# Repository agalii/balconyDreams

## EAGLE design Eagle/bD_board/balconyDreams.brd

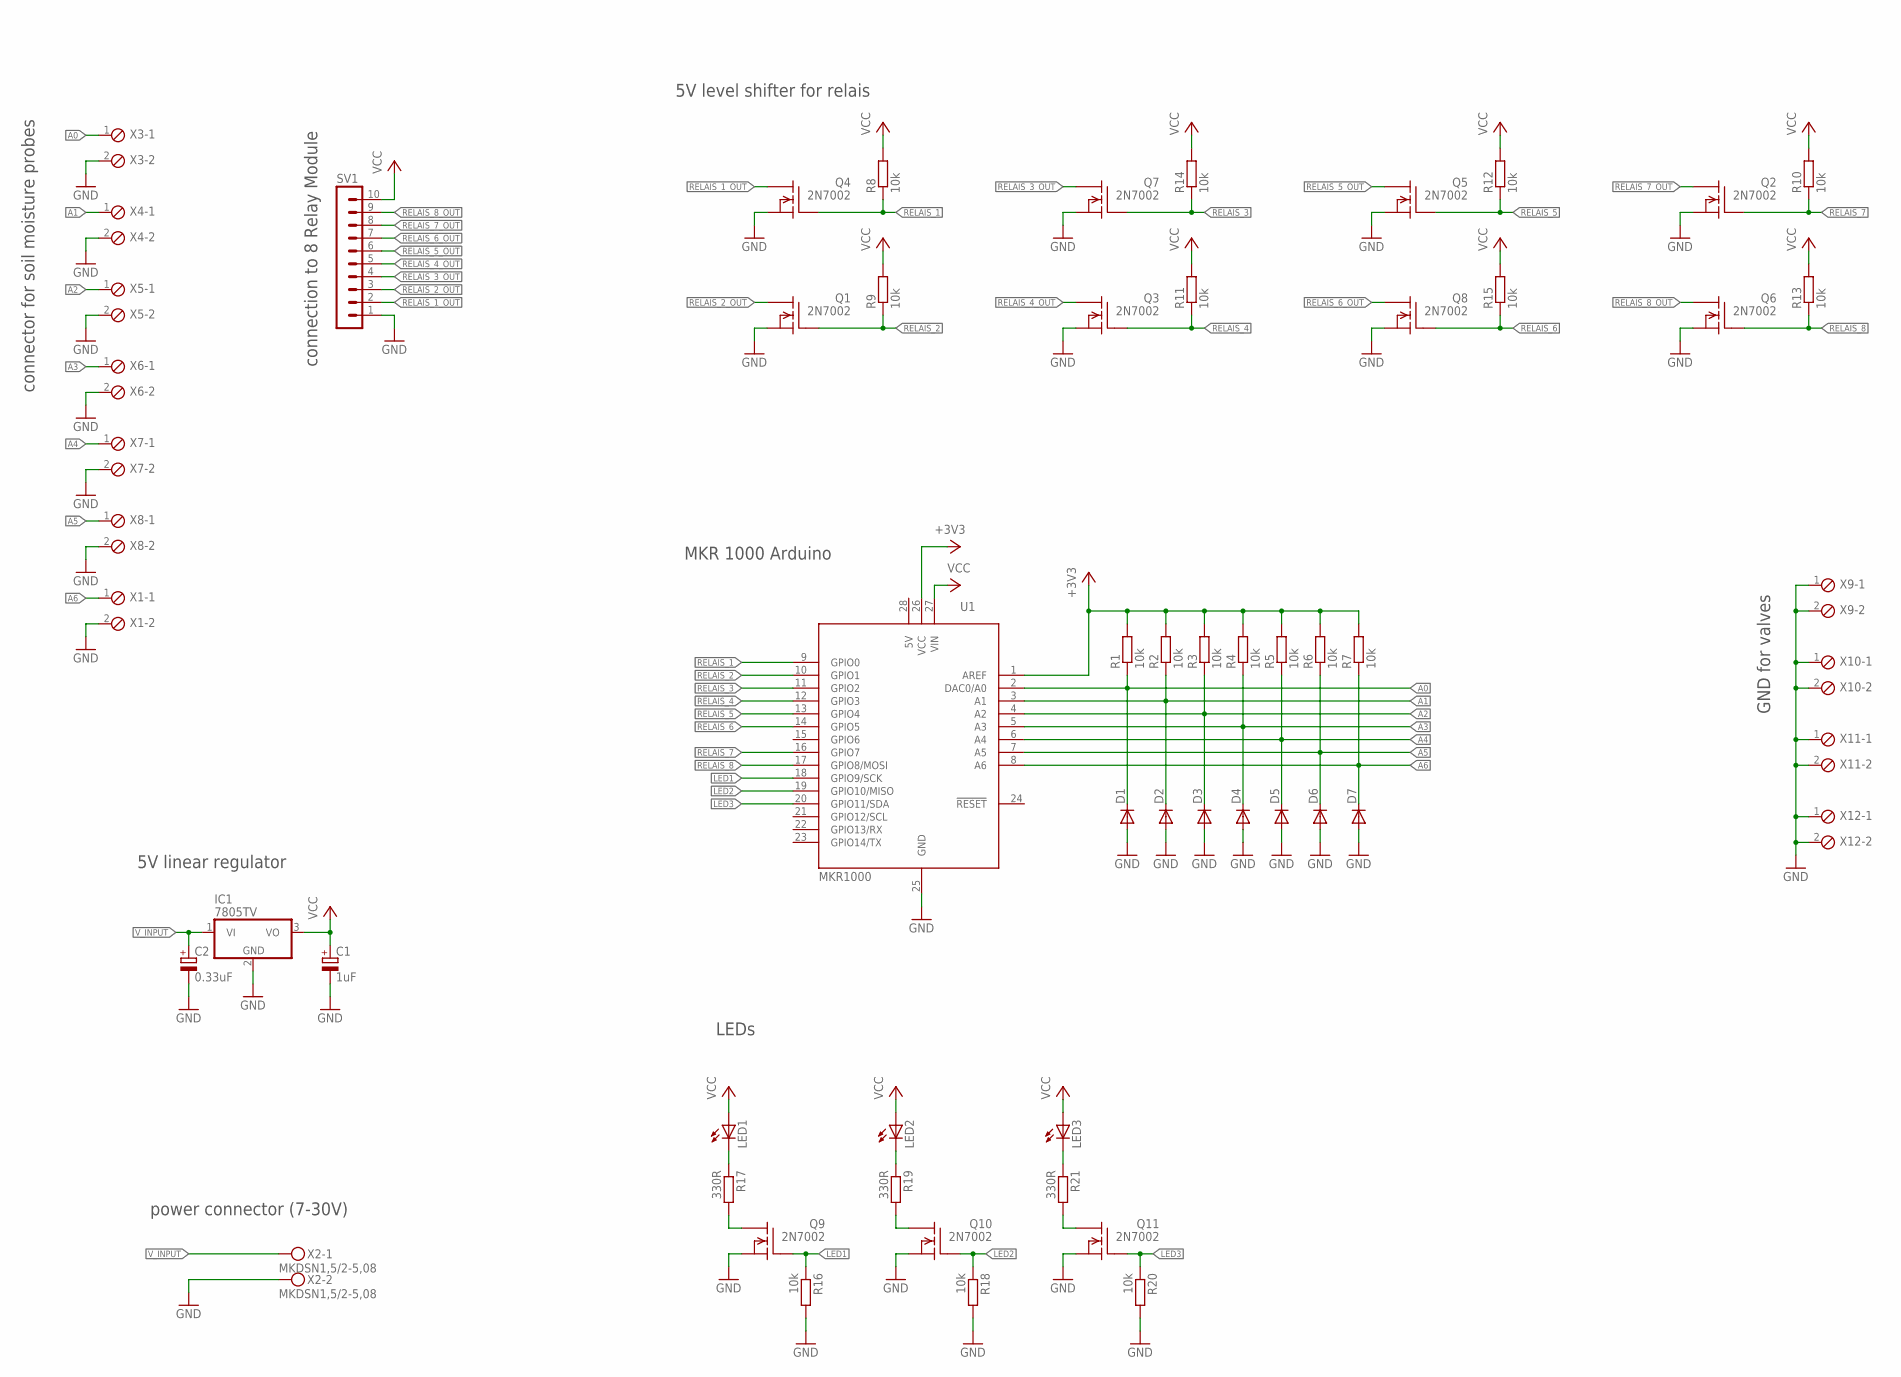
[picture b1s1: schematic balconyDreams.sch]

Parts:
C1: 1uF; E5-6
C2: 0.33uF; E5-6
D1, D2, D3, D4, D5, D6, D7: DIODE-SOD323-W; SOD323-W
IC1: 7805TV; TO220V
LED1, LED2, LED3: LEDCHIPLED_0805; CHIPLED_0805
Q1, Q2, Q3, Q4, Q5, Q6, Q7, Q8, Q9, Q10, Q11: 2N7002; SOT23
R1, R2, R3, R4, R5, R6, R7, R8, R9, R10, R11, R12, R13, R14, R15, R16, R18, R20: 10k; R0805
R17, R19, R21: 330R; R0805
SV1: MA10-1
U1: MKR1000
X1, X3, X4, X5, X6, X7, X8, X9, X10, X11, X12: MPT2; 2POL254
X2: MKDSN1,5/2-5,08

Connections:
+3V3: R1.2, R2.2, R3.2, R4.2, R5.2, R6.2, R7.2, U1.1 (AREF), U1.26 (VCC)
A0: D1.C, R1.1, U1.2 (DAC0/A0), X3.1
A1: D2.C, R2.1, U1.3 (A1), X4.1
A2: D3.C, R3.1, U1.4 (A2), X5.1
A3: D4.C, R4.1, U1.5 (A3), X6.1
A4: D5.C, R5.1, U1.6 (A4), X7.1
A5: D6.C, R6.1, U1.7 (A5), X8.1
A6: D7.C, R7.1, U1.8 (A6), X1.1
GND: C1.-, C2.-, D1.A, D2.A, D3.A, D4.A, D5.A, D6.A, D7.A, IC1.2 (GND), Q1.2 (S), Q2.2 (S), Q3.2 (S), Q4.2 (S), Q5.2 (S), Q6.2 (S), Q7.2 (S), Q8.2 (S), Q9.2 (S), Q10.2 (S), Q11.2 (S), R16.2, R18.2, R20.2, SV1.1, U1.25 (GND), X1.2, X2.2, X3.2, X4.2, X5.2, X6.2, X7.2, X8.2, X9.1, X9.2, X10.1, X10.2, X11.1, X11.2, X12.1, X12.2
LED1: Q9.1 (G), R16.1, U1.18 (GPIO9/SCK)
LED2: Q10.1 (G), R18.1, U1.19 (GPIO10/MISO)
LED3: Q11.1 (G), R20.1, U1.20 (GPIO11/SDA)
unnamed: LED1.C, R17.1
unnamed: Q9.3 (D), R17.2
unnamed: Q10.3 (D), R19.2
unnamed: LED2.C, R19.1
unnamed: Q11.3 (D), R21.2
unnamed: LED3.C, R21.1
RELAIS_1: Q4.1 (G), R8.1, U1.9 (GPIO0)
RELAIS_1_OUT: Q4.3 (D), SV1.2
RELAIS_2: Q1.1 (G), R9.1, U1.10 (GPIO1)
RELAIS_2_OUT: Q1.3 (D), SV1.3
RELAIS_3: Q7.1 (G), R14.1, U1.11 (GPIO2)
RELAIS_3_OUT: Q7.3 (D), SV1.4
RELAIS_4: Q3.1 (G), R11.1, U1.12 (GPIO3)
RELAIS_4_OUT: Q3.3 (D), SV1.5
RELAIS_5: Q5.1 (G), R12.1, U1.13 (GPIO4)
RELAIS_5_OUT: Q5.3 (D), SV1.6
RELAIS_6: Q8.1 (G), R15.1, U1.14 (GPIO5)
RELAIS_6_OUT: Q8.3 (D), SV1.7
RELAIS_7: Q2.1 (G), R10.1, U1.16 (GPIO7)
RELAIS_7_OUT: Q2.3 (D), SV1.8
RELAIS_8: Q6.1 (G), R13.1, U1.17 (GPIO8/MOSI)
RELAIS_8_OUT: Q6.3 (D), SV1.9
VCC: C1.+, IC1.3 (VO), LED1.A, LED2.A, LED3.A, R8.2, R9.2, R10.2, R11.2, R12.2, R13.2, R14.2, R15.2, SV1.10, U1.27 (VIN)
V_INPUT: C2.+, IC1.1 (VI), X2.1

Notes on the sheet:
connection to 8 Relay Module
5V level shifter for relais
connector for soil moisture probes
MKR 1000 Arduino
LEDs
5V linear regulator
power connector (7-30V)
GND for valves

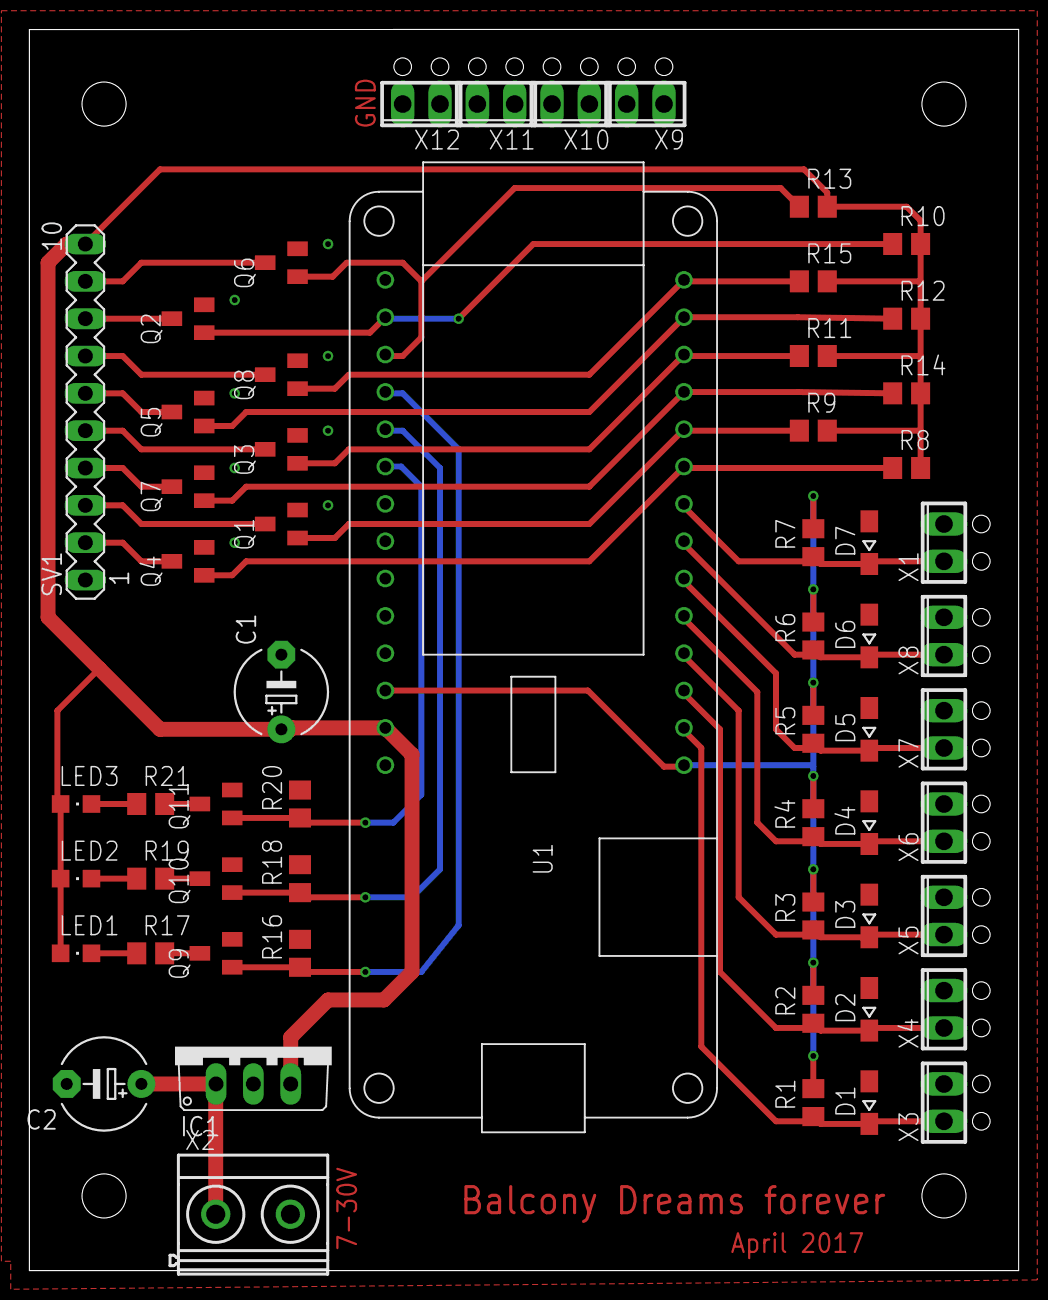
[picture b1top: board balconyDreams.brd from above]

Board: 2 copper layers, 67.3 x 84.5 mm, 59 parts (0 on the bottom side), 36 nets.

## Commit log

2016-05-08 new folder structure
2016-05-08 add some test programs and copy'n paste templates
2016-05-09 turn wifi code into reusable state machine implementation
2016-05-22 add sources for quick'n dirty balcony hack
2016-05-22 some state machine code cleanups
2016-05-22 wifi-udp: add 2nd state machine as demo
2017-04-27 add mkr1000 eagle library
2017-04-28 first prototype of eagle board and schematic
2017-04-28 add 2n7001 mosfets for relais outputs
2017-04-28 add mosfets for all relais outputs
2017-04-29 wired resistors replaced by SMD
2017-04-29 Lots of stuff - ready for review
2017-04-29 add gitignore
2017-04-30 add GND connectors for valves
2017-05-01 add additional vias for GND
2017-05-25 Add first version of firmware for MKR1000
    Implements some state machines and a hard-coded mapping from sensors to
    valves.
2017-05-25 Firmware: improve measurement debug log
2017-05-28 Some more cleanups
    * Do measurement from a timer
    * Allow different times for each valve
2017-06-03 Update mapping
